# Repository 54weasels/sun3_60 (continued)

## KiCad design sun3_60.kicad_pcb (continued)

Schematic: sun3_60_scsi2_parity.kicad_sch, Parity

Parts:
U710, U711, U712, U713: AS286; DIP-14_W7.62mm
U714: PAL16L8; DIP-20_W7.62mm
U715: PAL20R4; DIP-24_W7.62mm
U720, U721, U722, U723: ALS374; ALS373

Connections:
/CAS-: U715.6 (I4); also elsewhere on the board
/CLK: U715.1 (CLK); also elsewhere on the board
/CX0: U723.13 (D4); also elsewhere on the board
/CX1: U723.14 (D5); also elsewhere on the board
/CX2: U723.17 (D6); also elsewhere on the board
/DMA: U723.18 (D7); also elsewhere on the board
/EN.DEV-: U715.4 (I2); also elsewhere on the board
/Ethernet/A0: U720.3 (D0); also elsewhere on the board
/Ethernet/A1: U720.4 (D1); also elsewhere on the board
/Ethernet/A2: U720.7 (D2); also elsewhere on the board
/Ethernet/A3: U720.8 (D3); also elsewhere on the board
/Ethernet/A4: U720.13 (D4); also elsewhere on the board
/Ethernet/A5: U720.14 (D5); also elsewhere on the board
/Ethernet/A6: U720.17 (D6); also elsewhere on the board
/Ethernet/A7: U720.18 (D7); also elsewhere on the board
/Ethernet/A8: U721.3 (D0); also elsewhere on the board
/Ethernet/A9: U721.4 (D1); also elsewhere on the board
/Ethernet/A10: U721.7 (D2); also elsewhere on the board
/Ethernet/A11: U721.8 (D3); also elsewhere on the board
/Ethernet/A12: U721.13 (D4); also elsewhere on the board
/Ethernet/A13: U721.14 (D5); also elsewhere on the board
/Ethernet/A14: U721.17 (D6); also elsewhere on the board
/Ethernet/A15: U721.18 (D7); also elsewhere on the board
/Ethernet/A16: U722.3 (D0); also elsewhere on the board
/Ethernet/A17: U722.4 (D1); also elsewhere on the board
/Ethernet/A18: U722.7 (D2); also elsewhere on the board
/Ethernet/A19: U722.8 (D3); also elsewhere on the board
/Ethernet/A20: U722.13 (D4); also elsewhere on the board
/Ethernet/A21: U722.14 (D5); also elsewhere on the board
/Ethernet/A22: U722.17 (D6); also elsewhere on the board
/Ethernet/A23: U722.18 (D7); also elsewhere on the board
/Ethernet/A24: U723.3 (D0); also elsewhere on the board
/Ethernet/A25: U723.4 (D1); also elsewhere on the board
/Ethernet/A26: U723.7 (D2); also elsewhere on the board
/Ethernet/A27: U723.8 (D3); also elsewhere on the board
/INIT-: U714.3 (I3), U715.2 (I0); also elsewhere on the board
/P0: U713.6 (P_I/O); also elsewhere on the board
/P1: U712.6 (P_I/O); also elsewhere on the board
/P2: U711.6 (P_I/O); also elsewhere on the board
/P3: U710.6 (P_I/O); also elsewhere on the board
/R/W-: U715.5 (I3); also elsewhere on the board
/SCSI 2, Parity/IO.D0: U715.20 (Q2), U720.2 (Q0), U721.2 (Q0), U722.2 (Q0), U723.2 (Q0); also elsewhere on the board
/SCSI 2, Parity/IO.D1: U715.19 (Q3), U720.5 (Q1), U721.5 (Q1), U722.5 (Q1), U723.5 (Q1); also elsewhere on the board
/SCSI 2, Parity/IO.D2: U715.18 (Q4), U720.6 (Q2), U721.6 (Q2), U722.6 (Q2), U723.6 (Q2); also elsewhere on the board
/SCSI 2, Parity/IO.D3: U715.17 (Q5), U720.9 (Q3), U721.9 (Q3), U722.9 (Q3), U723.9 (Q3); also elsewhere on the board
/SCSI 2, Parity/IO.D4: U714.15 (IO5), U720.12 (Q4), U721.12 (Q4), U722.12 (Q4), U723.12 (Q4); also elsewhere on the board
/SCSI 2, Parity/IO.D5: U714.14 (IO6), U720.15 (Q5), U721.15 (Q5), U722.15 (Q5), U723.15 (Q5); also elsewhere on the board
/SCSI 2, Parity/IO.D6: U714.13 (IO7), U720.16 (Q6), U721.16 (Q6), U722.16 (Q6), U723.16 (Q6); also elsewhere on the board
/SCSI 2, Parity/IO.D7: U714.12 (IO8), U720.19 (Q7), U721.19 (Q7), U722.19 (Q7), U723.19 (Q7); also elsewhere on the board
/SCSI 2, Parity/PAR0-: U713.5 (P_ERR), U715.11 (I9)
/SCSI 2, Parity/PAR1-: U712.5 (P_ERR), U715.10 (I8)
/SCSI 2, Parity/PAR2-: U711.5 (P_ERR), U715.9 (I7)
/SCSI 2, Parity/PAR3-: U710.5 (P_ERR), U715.8 (I6)
/SCSI 2, Parity/PAR.CHK-: U714.17 (I03), U715.23 (I11)
/SCSI 2, Parity/PAR.ERR-: U714.4 (I4), U715.21 (IQ1)
/SCSI 2, Parity/PAR.IRQ-: U714.19 (IO1); also elsewhere on the board
/SCSI 2, Parity/PAR.SAMPLE: U715.16 (IQ6), U720.11 (CLK), U721.11 (CLK), U722.11 (CLK), U723.11 (CLK)
/SCSI 2, Parity/PAR.TEST-: U710.4 (P9), U711.4 (P9), U712.4 (P9), U713.4 (P9), U714.18 (IO2)
/SCSI 2, Parity/RD.PAR0-: U714.2 (I2), U715.13 (OE); also elsewhere on the board
/SCSI 2, Parity/RD.PAR4-: U723.1 (OE-); also elsewhere on the board
/SCSI 2, Parity/RD.PAR5-: U722.1 (OE-); also elsewhere on the board
/SCSI 2, Parity/RD.PAR6-: U721.1 (OE-); also elsewhere on the board
/SCSI 2, Parity/RD.PAR7-: U720.1 (OE-); also elsewhere on the board
/SCSI 2, Parity/WR.PAR0-: U714.1 (I1); also elsewhere on the board
/SCSI 2, Parity/WR.PAR4-: U715.3 (I1); also elsewhere on the board
/TEST4-: U715.14 (I10); also elsewhere on the board
/TEST6-: U714.11 (I10); also elsewhere on the board
/WRITE-: U710.3 (XMIT-), U711.3 (XMIT-), U712.3 (XMIT-), U713.3 (XMIT-); also elsewhere on the board
/XACK-: U715.7 (I5); also elsewhere on the board
/sun3_60_cpu/D0: U710.8 (P1); also elsewhere on the board
/sun3_60_cpu/D1: U710.9 (P2); also elsewhere on the board
/sun3_60_cpu/D2: U710.10 (P3); also elsewhere on the board
/sun3_60_cpu/D3: U710.11 (P4); also elsewhere on the board
/sun3_60_cpu/D4: U710.12 (P5); also elsewhere on the board
/sun3_60_cpu/D5: U710.13 (P6); also elsewhere on the board
/sun3_60_cpu/D6: U710.1 (P7); also elsewhere on the board
/sun3_60_cpu/D7: U710.2 (P8); also elsewhere on the board
/sun3_60_cpu/D8: U711.8 (P1); also elsewhere on the board
/sun3_60_cpu/D9: U711.9 (P2); also elsewhere on the board
/sun3_60_cpu/D10: U711.10 (P3); also elsewhere on the board
/sun3_60_cpu/D11: U711.11 (P4); also elsewhere on the board
/sun3_60_cpu/D12: U711.12 (P5); also elsewhere on the board
/sun3_60_cpu/D13: U711.13 (P6); also elsewhere on the board
/sun3_60_cpu/D14: U711.1 (P7); also elsewhere on the board
/sun3_60_cpu/D15: U711.2 (P8); also elsewhere on the board
/sun3_60_cpu/D16: U712.8 (P1); also elsewhere on the board
/sun3_60_cpu/D17: U712.9 (P2); also elsewhere on the board
/sun3_60_cpu/D18: U712.10 (P3); also elsewhere on the board
/sun3_60_cpu/D19: U712.11 (P4); also elsewhere on the board
/sun3_60_cpu/D20: U712.12 (P5); also elsewhere on the board
/sun3_60_cpu/D21: U712.13 (P6); also elsewhere on the board
/sun3_60_cpu/D22: U712.1 (P7); also elsewhere on the board
/sun3_60_cpu/D23: U712.2 (P8); also elsewhere on the board
/sun3_60_cpu/D24: U713.8 (P1); also elsewhere on the board
/sun3_60_cpu/D25: U713.9 (P2); also elsewhere on the board
/sun3_60_cpu/D26: U713.10 (P3); also elsewhere on the board
/sun3_60_cpu/D27: U713.11 (P4); also elsewhere on the board
/sun3_60_cpu/D28: U713.12 (P5); also elsewhere on the board
/sun3_60_cpu/D29: U713.13 (P6); also elsewhere on the board
/sun3_60_cpu/D30: U713.1 (P7); also elsewhere on the board
/sun3_60_cpu/D31: U713.2 (P8); also elsewhere on the board
GND: U710.7 (GND), U711.7 (GND), U712.7 (GND), U713.7 (GND), U714.5 (I5), U714.6 (I6), U714.7 (I7), U714.8 (I8), U714.9 (I9), U714.10 (GND), U715.12 (GND), U720.10 (GND), U721.10 (GND), U722.10 (GND), U723.10 (GND); also elsewhere on the board
VCC: U710.14 (VCC), U711.14 (VCC), U712.14 (VCC), U713.14 (VCC), U714.20 (VCC), U715.24 (VCC), U720.20 (VCC), U721.20 (VCC), U722.20 (VCC), U723.20 (VCC); also elsewhere on the board

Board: 4 copper layers, 225 parts (0 on the bottom side), 417 nets, no tracks yet.

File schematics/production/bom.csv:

Designator,Footprint,Quantity,Value,LCSC Part #
C199,C_Disc_D3.0mm_W2.0mm_P2.50mm,1,0.1UF,
C300,C_Disc_D3.0mm_W2.0mm_P2.50mm,1,18-PF,
C301,C_Radial_D6.3mm_H5.0mm_P2.50mm,1,9-35PF,
"C500, C501",C_Rect_L7.0mm_W2.0mm_P5.00mm,2,20 pF,
C502,C_Rect_L7.0mm_W2.0mm_P5.00mm,1,680 pF,
"C503, C504, X1, X10, X11, X12, X13, X14, X15, X16, X17, X18, X19, X2, X20, X21, X22, X23, X24, X25, X26, X27, X28, X29, X3, X30, X31, X32, X33, X34, X35, X36, X37, X38, X39, X4, X40, X41, X42, X43, X44, X45, X46, X47, X48, X49, X5, X50, X51, X52, X53, X54, X55, X56, X57, X58, X59, X6, X60, X61, X62, X63, X64, X65, X66, X67, X68, X69, X7, X70, X71, X72, X73, X74, X75, X76, X77, X78, X79, X8, X80, X9",C_Rect_L7.0mm_W2.0mm_P5.00mm,82,0.1uF,
C505,C_Rect_L7.0mm_W2.0mm_P5.00mm,1,0.0056uF,
J11,TE_MATE-N-LOK_350211-1_1x04_P5.08mm_Vertical,1,Conn_01x04_Pin,
J2,PinHeader_1x05_P2.54mm_Vertical,1,Serial A/B,
J200,PinHeader_1x03_P2.54mm_Vertical,1,DIAG,
J3,PinHeader_1x09_P2.54mm_Vertical,1,Ethernet,
K199,CP_Radial_Tantal_D6.0mm_P2.50mm,1,10UF,
K500,CP_Radial_Tantal_D6.0mm_P2.50mm,1,10 uF,
"K900, K901, K903, K904",CP_Radial_D10.0mm_P5.00mm,4,1000uF,
R100,R_Axial_DIN0207_L6.3mm_D2.5mm_P7.62mm_Horizontal,1,150 ohm,
R101,R_Axial_DIN0207_L6.3mm_D2.5mm_P7.62mm_Horizontal,1,100 ohm,
R300,R_Axial_DIN0207_L6.3mm_D2.5mm_P7.62mm_Horizontal,1,200Kohm,
R301,R_Axial_DIN0207_L6.3mm_D2.5mm_P7.62mm_Horizontal,1,470-OHM,
R501,R_Axial_DIN0207_L6.3mm_D2.5mm_P7.62mm_Horizontal,1,510 Ohm,
R502,R_Axial_DIN0207_L6.3mm_D2.5mm_P7.62mm_Horizontal,1,3K Ohm,
"S109, S111, S117, S120, S121, S122, S123, S124, S125, S126, S127, S800",R_Array_SIP10,12,4.7k Ohm,
"S113, S115, S116",R_Array_SIP10,3,470 Ohm,
"S114, S502",R_Array_SIP10,2,1k Ohm,
S200,R_Array_SIP8,1,68 Ohm,
S400,R_Array_SIP8,1,4.7K Ohm,
S500,R_Array_SIP10,1,40.2 Ohm 1%,
U100,68020,1,68020,
"U102, U103, U106, U230, U231, U232, U518, U519, U714, U800, U805",DIP-20_W7.62mm,11,PAL16L8,
"U104, U600",DIP-14_W7.62mm,2,74F04,
U107,DIP-24_W7.62mm,1,PAL20X10,
U108,DIP-14_W7.62mm,1,74F00,
U110,Oscillator_DIP-14,1,40.000 Mhz,
U113,DIP-14_W7.62mm,1,74AS74,
"U114, U520",DIP-16_W7.62mm,2,74F175,
U115,DIP-16_W7.62mm,1,74LS590,
"U122, U720, U721, U722, U723",DIP-20_W7.62mm,5,ALS374,
"U123, U226, U305, U510, U511, U512",DIP-20_W7.62mm,6,ALS373,
U130,DIP-20_W7.62mm,1,74F374,
U131,DIP-20_W7.62mm,1,PAL16R6,
U132,DIP-20_W7.62mm,1,ALS244,
U199,DIP-8_W7.62mm,1,7705,
"U200, U201",DIP-22_W7.62mm,2,7188,
U2003,DIP-14_W7.62mm,1,74AS04,
U2004,DIP-14_W7.62mm,1,74LS125,
"U202, U203, U205, U206, U207, U208",DIP-20_W7.62mm,6,2168,
U210,DIP-16_W7.62mm,1,LS2518,
"U212, U213, U215, U217, U218",DIP-20_W7.62mm,5,ALS245,
U223,DIP-20_W7.62mm,1,74F534,
U224,DIP-16_W7.62mm,1,AM27S19,
"U225, U227, U304",DIP-20_W7.62mm,3,ALS273,
"U228, U229",PinHeader_2x04_P2.54mm_Vertical,2,LED_Block,
U300,DIP-28_W15.24mm,1,27512,
U301,DIP-24_W15.24mm,1,28C16,
U302,DIP-24_W15.24mm,1,7170,
U303,Crystal_AT310_D3.0mm_L10.0mm_Horizontal,1,32768Hz,
"U307, U310, U311, U802",DIP-24_W7.62mm,4,PAL20L8,
U309,Battery_Panasonic_CR2032-VS1N_Vertical_CircularHoles,1,3-VOLT,
U312,DIP-24_W7.62mm,1,PAL8L14,
U313,DIP-20_W7.62mm,1,PAL16R4,
U401,DIP-40_W15.24mm,1,Z8530,
U402,Oscillator_DIP-8,1,4.9152 Mhz,
U408,DIP-14_W7.62mm,1,74LS04,
U500,DIP-48_W15.24mm,1,AM7990,
U501,DIP-24_W7.62mm,1,AM7992,
U502,Crystal_HC49-U_Vertical,1,20 Mhz,
U503,DIP-16_W7.62mm,1,TRANSF,
"U514, U515, U516, U517",DIP-24_W7.62mm,4,ALS652,
"U710, U711, U712, U713",DIP-14_W7.62mm,4,AS286,
U715,DIP-24_W7.62mm,1,PAL20R4,
U801,DIP-16_W7.62mm,1,74AS257,
"U803, U804",DIP-14_W7.62mm,2,74F64,
"U900, U901, U902, U903",PinHeader_1x30_P2.54mm_Vertical,4,SIMM,
"U904, U905, U906",DIP-16_W7.62mm,3,74AS258,
"U907, U908",DIP-14_W7.62mm,2,AS1032,
U909,DIP-16_W7.62mm,1,22 Ohm,
X301,CP_Radial_D10.0mm_P5.00mm,1,470UF,

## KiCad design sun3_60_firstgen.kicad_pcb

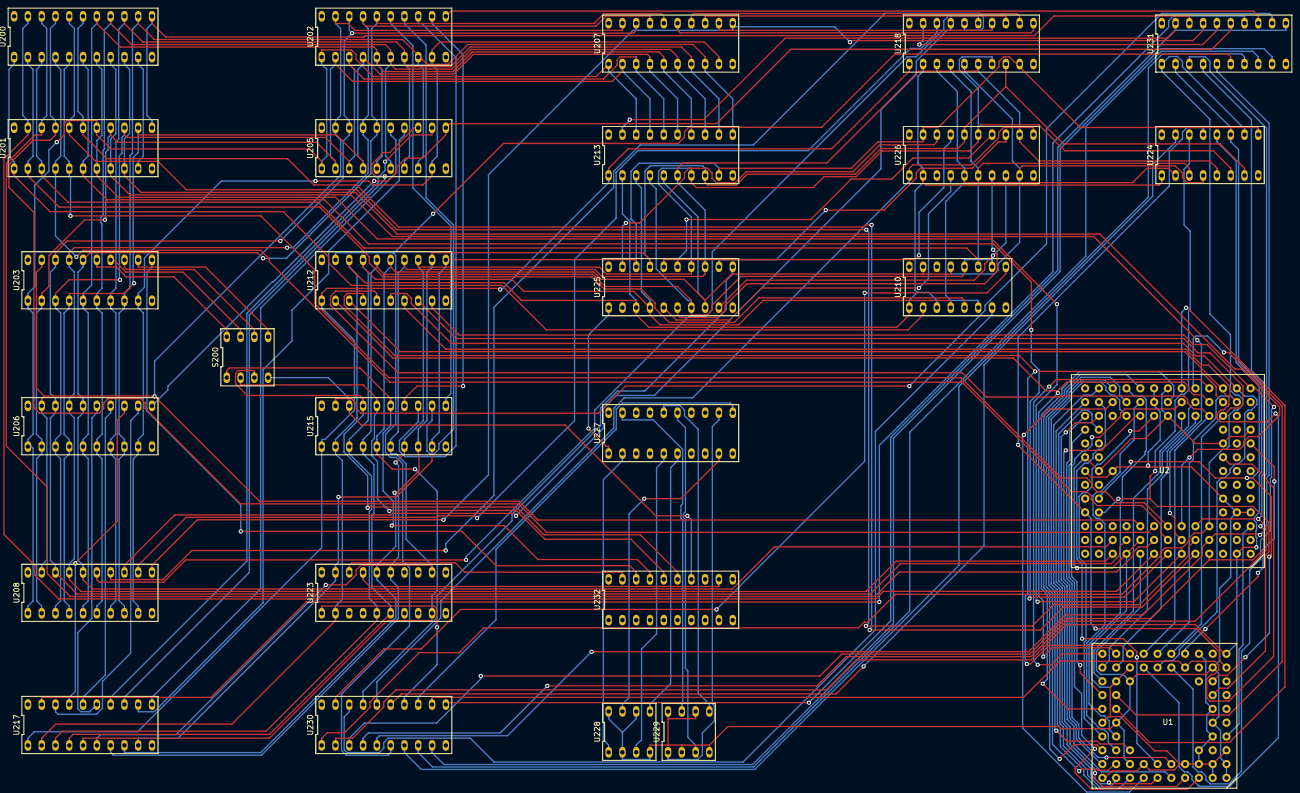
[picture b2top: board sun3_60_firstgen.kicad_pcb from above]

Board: 2 copper layers, 27 parts (0 on the bottom side), 149 nets.

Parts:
S200: 68-ohm; DIP-8_296_ELL
U1: 68881
U2: 68020
U200, U201: 7188
U202, U203, U205, U206, U207, U208: 2168
U210: LS2518
U212, U213, U215, U217, U218: ALS245
U223: 74F534; F534
U224: AM27S19
U225, U227: ALS273
U226: ALS373; ALS273
U228, U229: LED_Block; DIP-8_296_ELL
U230, U231, U232: PAL16L8; DIP-20_296_ELL

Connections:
/sun3_60_cpu/A0: U2.30, U224.10, U230.1, U231.1
/sun3_60_cpu/A1: U1.91, U2.2, U224.11, U230.2, U231.2
/sun3_60_cpu/A2: U1.72, U2.64, U224.12
/sun3_60_cpu/A3: U1.81, U2.52, U224.13
/sun3_60_cpu/A4: U1.62, U2.51, U224.14
/sun3_60_cpu/A13: U2.24, U202.16, U203.16, U205.16, U206.16, U207.16, U208.16
/sun3_60_cpu/A14: U2.11, U202.17, U203.17, U205.17, U206.17, U207.17, U208.17
/sun3_60_cpu/A15: U2.23, U202.18, U203.18, U205.18, U206.18, U207.18, U208.18
/sun3_60_cpu/A16: U2.35, U202.19, U203.19, U205.19, U206.19, U207.19, U208.19
/sun3_60_cpu/A17: U2.34, U200.19, U201.19
/sun3_60_cpu/A18: U2.21, U200.20, U201.20
/sun3_60_cpu/A19: U2.8, U200.21, U201.21
/sun3_60_cpu/A20: U2.20, U200.4, U201.4
/sun3_60_cpu/A21: U2.33, U200.5, U201.5
/sun3_60_cpu/A22: U2.7, U200.6, U201.6
/sun3_60_cpu/A23: U2.6, U200.7, U201.7
/sun3_60_cpu/A24: U2.19, U200.8, U201.8
/sun3_60_cpu/A25: U2.32, U200.9, U201.9
/sun3_60_cpu/A26: U2.5, U200.17, U201.17
/sun3_60_cpu/A27: U2.18, U200.18, U201.18
/sun3_60_cpu/A28: U2.4, U230.3, U231.3
/sun3_60_cpu/A29: U2.31, U230.4, U231.4
/sun3_60_cpu/A30: U2.17, U230.5, U231.5
/sun3_60_cpu/D0: U1.3, U2.130
/sun3_60_cpu/D1: U1.4, U2.129
/sun3_60_cpu/D2: U1.15, U2.143
/sun3_60_cpu/D3: U1.5, U2.142
/sun3_60_cpu/D4: U1.6, U2.156
/sun3_60_cpu/D5: U1.16, U2.155
/sun3_60_cpu/D6: U1.7, U2.154
/sun3_60_cpu/D7: U1.8, U2.140
/sun3_60_cpu/D8: U1.9, U2.168
/sun3_60_cpu/D9: U1.28, U2.167
/sun3_60_cpu/D10: U1.19, U2.153
/sun3_60_cpu/D11: U1.20, U2.139
/sun3_60_cpu/D12: U1.39, U2.166
/sun3_60_cpu/D13: U1.29, U2.152
/sun3_60_cpu/D14: U1.30, U2.165
/sun3_60_cpu/D15: U1.40, U2.138
/sun3_60_cpu/D16: U1.60, U2.150
/sun3_60_cpu/D17: U1.59, U2.162
/sun3_60_cpu/D18: U1.70, U2.149
/sun3_60_cpu/D19: U1.80, U2.136
/sun3_60_cpu/D20: U1.69, U2.161
/sun3_60_cpu/D21: U1.90, U2.148
/sun3_60_cpu/D22: U1.100, U2.160
/sun3_60_cpu/D23: U1.89, U2.135
/sun3_60_cpu/D24: U1.99, U2.147, U212.2
/sun3_60_cpu/D25: U1.87, U2.159, U212.3
/sun3_60_cpu/D26: U1.98, U2.146, U212.4
/sun3_60_cpu/D27: U1.97, U2.134, U212.5
/sun3_60_cpu/D28: U1.86, U2.158, U212.6
/sun3_60_cpu/D29: U1.96, U2.145, U212.7
/sun3_60_cpu/D30: U1.95, U2.133, U212.8
/sun3_60_cpu/D31: U1.85, U2.157, U212.9
/sun3_60_cpu/DSACK0-: U1.84, U2.94, U230.12
/sun3_60_cpu/DSACK1-: U1.94, U2.105
/sun3_60_mmu_diag/ACCESS: S200.6, U203.13
/sun3_60_mmu_diag/ACCESSX: S200.3, U215.17, U232.15
/sun3_60_mmu_diag/BERR.P-: U223.17, U232.12
/sun3_60_mmu_diag/BERR.V-: U223.18, U232.19
/sun3_60_mmu_diag/C.S3-: U230.8, U231.8
/sun3_60_mmu_diag/C.S5-: U230.9, U231.9
/sun3_60_mmu_diag/C.S7X-: U230.11, U231.11
/sun3_60_mmu_diag/CX0: U200.1, U201.1, U210.2
/sun3_60_mmu_diag/CX1: U200.2, U201.2, U210.5
/sun3_60_mmu_diag/CX2: U200.3, U201.3, U210.11
/sun3_60_mmu_diag/EN.BOOT-: U225.19, U226.18
/sun3_60_mmu_diag/EN.CTL-: U212.19, U230.6, U231.6
/sun3_60_mmu_diag/EN.FPP: U225.16, U226.17
/sun3_60_mmu_diag/EN.PMAP0-: U215.19, U231.12
/sun3_60_mmu_diag/EN.PMAP2-: U217.19, U231.14
/sun3_60_mmu_diag/EN.PMAP3-: U218.19, U231.16
/sun3_60_mmu_diag/EN.SMAP-: U213.19, U231.19
/sun3_60_mmu_diag/EN.VIDEO: U225.9, U226.8
/sun3_60_mmu_diag/INIT-: U225.1, U227.1
/sun3_60_mmu_diag/LED0: U227.2, U228.1
/sun3_60_mmu_diag/LED1: U227.5, U228.3
/sun3_60_mmu_diag/LED2: U227.6, U228.5
/sun3_60_mmu_diag/LED3: U227.9, U228.7
/sun3_60_mmu_diag/LED4: U227.12, U229.1
/sun3_60_mmu_diag/LED5: U227.15, U229.3
/sun3_60_mmu_diag/LED6: U227.16, U229.5
/sun3_60_mmu_diag/LED7: U227.19, U229.7
/sun3_60_mmu_diag/MMU0: U210.1, U210.3, U212.18, U213.2, U215.2, U217.2, U218.2, U223.2, U224.1, U225.3, U226.2
/sun3_60_mmu_diag/MMU1: U210.4, U210.6, U212.17, U213.3, U215.3, U217.3, U218.3, U223.5, U224.2, U225.4, U226.5
/sun3_60_mmu_diag/MMU2: U210.10, U210.12, U212.16, U213.4, U215.4, U217.4, U218.4, U223.6, U224.3, U225.7, U226.6
/sun3_60_mmu_diag/MMU3: U210.13, U210.15, U212.15, U213.5, U215.5, U217.5, U218.5, U223.9, U224.4, U225.8, U226.9
/sun3_60_mmu_diag/MMU4: U212.14, U213.6, U215.6, U217.6, U218.6, U223.12, U224.5, U225.13, U226.12
/sun3_60_mmu_diag/MMU5: U212.13, U213.7, U215.7, U217.7, U218.7, U223.15, U224.6, U225.14, U226.15
/sun3_60_mmu_diag/MMU6: U212.12, U213.8, U215.8, U217.8, U218.8, U223.16, U224.7, U225.17, U226.16
/sun3_60_mmu_diag/MMU7: U212.11, U213.9, U215.9, U217.9, U218.9, U223.19, U224.9, U225.18, U226.19
/sun3_60_mmu_diag/MMU.S: U202.13, U215.13
/sun3_60_mmu_diag/MMU.V: U202.15, U215.11
/sun3_60_mmu_diag/MMU.W: U202.14, U215.12
/sun3_60_mmu_diag/MMU.X: U202.12, U215.14
/sun3_60_mmu_diag/MODIFY: S200.5, U203.12
/sun3_60_mmu_diag/MODIFYX: S200.4, U215.18, U232.14
/sun3_60_mmu_diag/PA13: U208.12, U218.18
/sun3_60_mmu_diag/PA14: U208.13, U218.17
/sun3_60_mmu_diag/PA15: U208.14, U218.16
/sun3_60_mmu_diag/PA16: U208.15, U218.15
/sun3_60_mmu_diag/PA17: U207.12, U218.14
/sun3_60_mmu_diag/PA18: U207.13, U218.13
/sun3_60_mmu_diag/PA19: U207.14, U218.12
/sun3_60_mmu_diag/PA20: U207.15, U218.11
/sun3_60_mmu_diag/PA21: U206.12, U217.18
/sun3_60_mmu_diag/PA22: U206.13, U217.17
/sun3_60_mmu_diag/PA23: U206.14, U217.16
/sun3_60_mmu_diag/PA24: U206.15, U217.15
/sun3_60_mmu_diag/PA25: U205.12, U217.14
/sun3_60_mmu_diag/PA26: U205.13, U217.13
/sun3_60_mmu_diag/PA27: U205.14, U217.12
/sun3_60_mmu_diag/PA28: U205.15, U217.11
/sun3_60_mmu_diag/PD0-: U200.10, U201.10
/sun3_60_mmu_diag/PD1-: U202.9, U203.9, U205.9, U206.9, U207.9, U208.9
/sun3_60_mmu_diag/RD.BERR-: U223.1, U230.14
/sun3_60_mmu_diag/RD.CX-: U210.7, U230.18
/sun3_60_mmu_diag/RD.ID-: U224.15, U230.15
/sun3_60_mmu_diag/RD.SYSEN-: U226.1, U226.11, U230.16
/sun3_60_mmu_diag/READ-: U212.1, U213.1, U215.1, U217.1, U218.1
/sun3_60_mmu_diag/SA17: U201.16, U202.1, U203.1, U205.1, U206.1, U207.1, U208.1, U213.18
/sun3_60_mmu_diag/SA18: U201.15, U202.2, U203.2, U205.2, U206.2, U207.2, U208.2, U213.17
/sun3_60_mmu_diag/SA19: U201.14, U202.3, U203.3, U205.3, U206.3, U207.3, U208.3, U213.16
/sun3_60_mmu_diag/SA20: U201.13, U202.4, U203.4, U205.4, U206.4, U207.4, U208.4, U213.15
/sun3_60_mmu_diag/SA21: U200.16, U202.5, U203.5, U205.5, U206.5, U207.5, U208.5, U213.14
/sun3_60_mmu_diag/SA22: U200.15, U202.6, U203.6, U205.6, U206.6, U207.6, U208.6, U213.13
/sun3_60_mmu_diag/SA23: U200.14, U202.7, U203.7, U205.7, U206.7, U207.7, U208.7, U213.12
/sun3_60_mmu_diag/SA24: U200.13, U202.8, U203.8, U205.8, U206.8, U207.8, U208.8, U213.11
/sun3_60_mmu_diag/TYPE0: S200.7, U203.14
/sun3_60_mmu_diag/TYPE0X: S200.2, U215.16, U232.16
/sun3_60_mmu_diag/TYPE1: S200.8, U203.15
/sun3_60_mmu_diag/TYPE1X: S200.1, U215.15, U232.17
/sun3_60_mmu_diag/WE.PMAP0-: U202.11, U231.13
/sun3_60_mmu_diag/WE.PMAP2-: U205.11, U206.11, U231.15
/sun3_60_mmu_diag/WE.PMAP3-: U207.11, U208.11, U231.17
/sun3_60_mmu_diag/WE.SMAP-: U200.12, U201.12, U231.18
/sun3_60_mmu_diag/WE.STAT-: U203.11, U232.18
/sun3_60_mmu_diag/WR.CX-: U210.9, U230.19
/sun3_60_mmu_diag/WR.DIAG-: U227.11, U230.13
/sun3_60_mmu_diag/WR.SYSEN-: U225.11, U230.17
/sun3_60_mmu_diag/WRITE-: U230.7, U231.7
GND: U1.2, U1.10, U1.12, U1.13, U1.14, U1.17, U1.21, U1.23, U1.32, U1.50, U1.52, U1.79, U1.88, U1.93, U2.10, U2.22, U2.90, U2.104, U2.107, U2.118, U2.137, U2.163
unnamed: U1.31, U2.27
unnamed: U225.5, U226.4
unnamed: U225.6, U226.7
unnamed: U225.12, U226.13
unnamed: U225.15, U226.14
VCC: U1.1, U1.11, U1.18, U1.42, U1.49, U1.78, U1.82, U2.9, U2.40, U2.41, U2.55, U2.89, U2.91, U2.151, U2.164, U228.2, U228.4, U228.6, U228.8, U229.2, U229.4, U229.6, U229.8

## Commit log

2025-03-08 First version of schematics
    Basic schematics for Sun 3/60 with some obvious corrections.
    CPU
    * 68030 support left out entirely
    * 68881 in the schematics but left out of the PCB
    MMU
    * U2001 which would be needed to support any video, either P4 or built-in not in the PCB
2025-03-08 clean up ignore files
2025-03-09 Initial layout
    - Lay out the PCB to match the original board sans the missing components. No routing yet.
    - Pick standard library footprints instead of custom ones for some components.
    - Change some ERC errors into warnings - like output pin connected to output pin.
    - Change resistor network S200 from DIP to SIP type.
    - Set Serial keyboard/mouse section to “Do Not Populate” to gain some space, and it wasn’t going to be used with no video possible anyway. However, in knockout testing with 3.0.1 boot PROM self tests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
    - Fix the LED blocks for the diag register to matc
2025-03-09 Update README.md for V2
2025-03-12 Routing
    - Initial routing with standard 4 layers setup
    - Add SIM holes
    - Copper to edge clearance 1.0mm
    - Relaxed the layout a little so the autorouter can have results
    - Moved K500 to the ethernet section it belongs to, and changed type. Same for K199
2025-03-12 Update README.md for V3
2025-05-24 Clean up before reorganizing the folders. The schematics and PCB reflect the fixes discovered during the prototype build.
2025-05-24 Clean up system files
2025-05-24 Move schematics to their own folder
2025-05-24 Add the production files for first version
2025-05-24 Update README.md with latest changes, change version scheme
2025-05-25 Add PDF schematics
2025-05-25 Update README.md with TODOs, FAQ
2025-05-25 Add the PAL images and other relevant softwre
2025-05-25 Create Readme.md for PALs folder
2025-05-25 Organize the PAL folder by type
2025-05-25 Update Readme.md with PAL types and positions
2025-05-25 Update Readme.md with more PAL information
2025-05-25 Add high-res photos of the original board
2025-05-25 Add a boot prom image
2025-05-25 Create Readme.md with known issues for the current production board
2025-05-26 Update Readme.md in build to mention issue with serial inverting buffer
2025-05-27 Add the original schematics and consolidate
2025-05-27 Create Readme.md for schematics PDF
2025-05-27 Add images of the V1 PCB
2025-05-27 More images, thermal scans of the board running
2025-05-27 Create Readme.md for bootprom
2025-05-28 Clean up some PAL documentation
2025-05-28 Clean up more PAL documentation
2025-06-01 Add a PLD file (for an ATF1504AS-10AU100) which attempts to consolidate U23[012] & U102 into a single CPLD. Mostly useful as documentation of the 3/60 MMU and memory/space map for now.
